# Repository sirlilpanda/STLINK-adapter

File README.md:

# STLINK adapter
this stlink adapter was made to allow easier access to an SWD interface, as well as interface with a 6-pin plug-o-nails connector. It also has indication leds for power, both 3.3v and 5v as well as a led for reset. As well as decoupling capactors(admittedly not needed) as test points to make sure you are programming and can read data back out.

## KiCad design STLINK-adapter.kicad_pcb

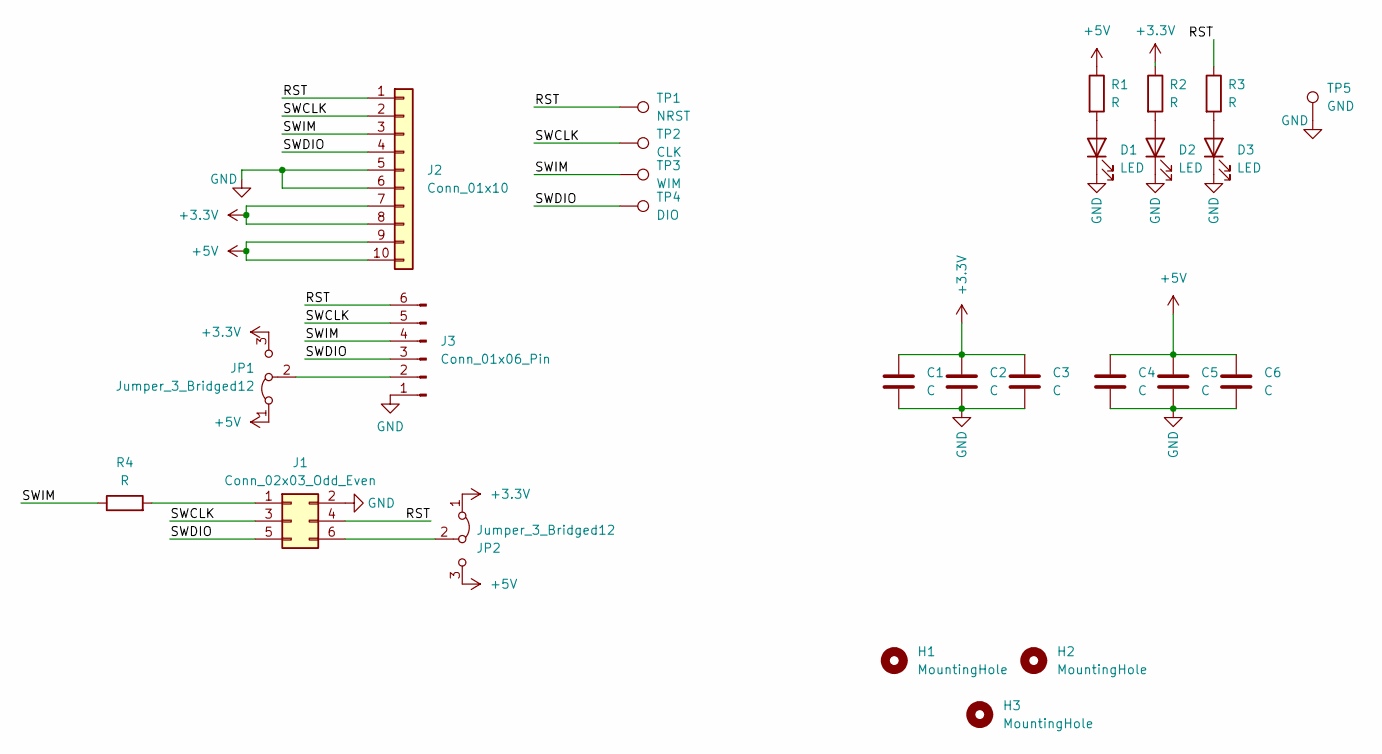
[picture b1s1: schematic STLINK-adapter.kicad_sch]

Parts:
C1, C2, C3, C4, C5, C6: C; C_0805_2012Metric
D1, D2, D3: LED; LED_0805_2012Metric
H1, H2, H3: MountingHole; MountingHole_3.2mm_M3_DIN965_Pad
J1: Conn_02x03_Odd_Even; PinHeader_2x03_P2.54mm_Vertical
J2: Conn_01x10; IDC-Header_2x05_P2.54mm_Vertical
J3: Conn_01x06_Pin; PinHeader_1x06_P2.54mm_Horizontal
JP1: Jumper_3_Bridged12; PinHeader_1x03_P2.54mm_Vertical
JP2: Jumper_3_Bridged12; SolderJumper-3_P1.3mm_Bridged2Bar12_Pad1.0x1.5mm_NumberLabe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
R1, R2, R3, R4: R; R_0805_2012Metric
TP1: NRST; TestPoint_Bridge_Pitch2.54mm_Drill1.3mm
TP2: CLK; TestPoint_Bridge_Pitch2.54mm_Drill1.3mm
TP3: WIM; TestPoint_Bridge_Pitch2.54mm_Drill1.3mm
TP4: DIO; TestPoint_Bridge_Pitch2.54mm_Drill1.3mm
TP5: GND; TestPoint_Bridge_Pitch2.54mm_Drill1.3mm

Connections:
+3.3V: C1.1, C2.1, C3.1, J2.7, J2.8, JP1.3 (B), JP2.1 (A), R2.1
+5V: C4.1, C5.1, C6.1, J2.9, J2.10, JP1.1 (A), JP2.3 (B), R1.1
/RST: J1.4, J2.1, J3.6, R3.1, TP1.1
/SWCLK: J1.3, J2.2, J3.5, TP2.1
/SWDIO: J1.5, J2.4, J3.3, TP4.1
/SWIM: J2.3, J3.4, R4.1, TP3.1
GND: C1.2, C2.2, C3.2, C4.2, C5.2, C6.2, D1.1 (K), D2.1 (K), D3.1 (K), J1.2, J2.5, J2.6, J3.1, TP5.1
unnamed: D1.2 (A), R1.2
unnamed: D2.2 (A), R2.2
unnamed: D3.2 (A), R3.2
unnamed: J1.1, R4.2
unnamed: J1.6, JP2.2 (C)
unnamed: J3.2, JP1.2 (C)

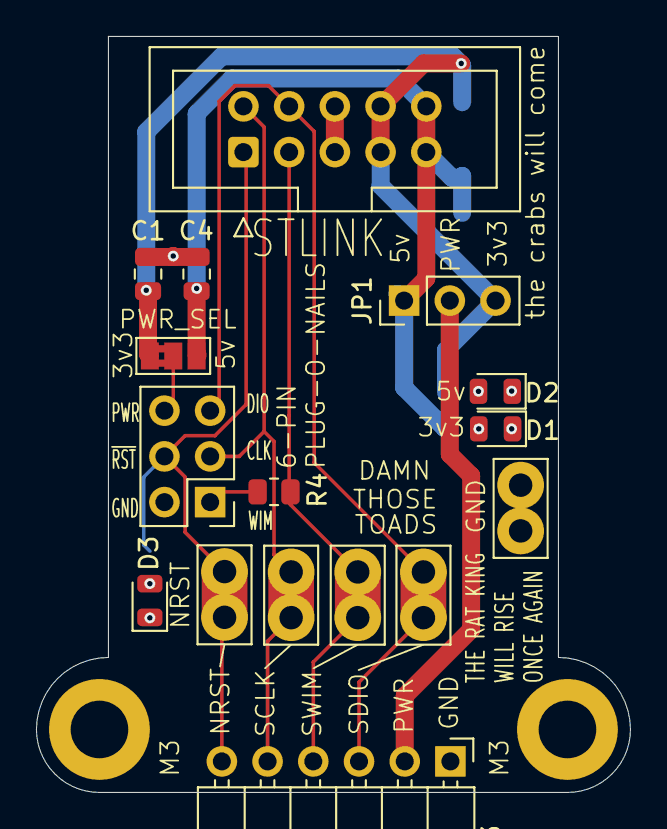
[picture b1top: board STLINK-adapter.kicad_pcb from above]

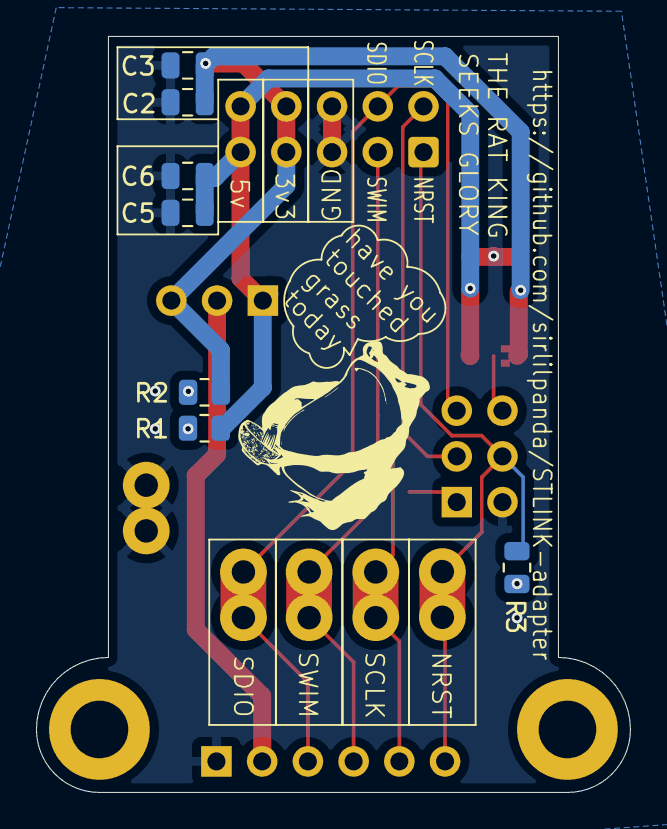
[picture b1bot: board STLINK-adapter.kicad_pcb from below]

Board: 2 copper layers, 33.0 x 42.0 mm, 25 parts (7 on the bottom side), 13 nets.

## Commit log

2024-05-17 inital commit
2024-05-17 added readme
2024-05-17 added comp values
